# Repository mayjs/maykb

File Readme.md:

#  Maykb - a custom split keyboard for ISO-DE users
Maykb is a split keyboard using a staggered ISO layout including the ISO-Enter. Other features are one duplicated column in the middle (for people who don't always use the same finger for those middle keys) and the inclusion of an additional key left of the `h` which I use as a backspace key.

## PCB
The PCBs for maykb are based on a STM32F103 and Cherry MX switches.
Both halves communicate using a UART interface and are equipped to be chainable, i.e. you could chain together more keyboards so you could add a numpad or a dedicated macropad if you wanted to.

There is also no fixed host MCU; both sides can act as the host and communicate over USB.

The initial revision of the PCB has one flaw: The voltage regulator for the MCU is not enabled properly due to a enable pin polarity mistake. Fixing this mistake involves lifting a pin of that regulator and wiring it properly.
I plan to replace the regulator eventually and fix the schematic and layout at that point as well.
As far as I know, there are no other hardware issues that would keep you from building one of these keyboards.

## Firmware
### Application
The firmware for the keyboard is written in Rust and uses [keyberon](https://github.com/TeXitoi/keyberon).
You need to build two different firmware versions for the left and right side so the firmware knows which part of the matrix it's working on.

### Bootloader
I'm using a slightly modified version of the [stm32duino-bootloader](https://github.com/rogerclarkmelbourne/STM32duino-bootloader).
This allows easy DFU flashing when you change the firmware.
The bootloader can be entered by holding the top left key of each side or by holding down the bootloader key on the bottom side of the PCB.

## Construction
The maykb case is designed to be 3D-printed and design files are available as OpenSCAD code.
It should be easy to adjust the code to allow for different screw tolerances or even brass screw inserts.

As a small novelty, the plates can be manufactured as aluminium PCBs (I had good results with JLCPCB), which is cheaper than all laser cutting services I was able to locate.
It should also be possible to export the plate PCB files as a DXF file and use another fabrication technique.

The PCB is a simple 1.6mm thick two layer PCB and should be easily manufactured at any prototyping company.

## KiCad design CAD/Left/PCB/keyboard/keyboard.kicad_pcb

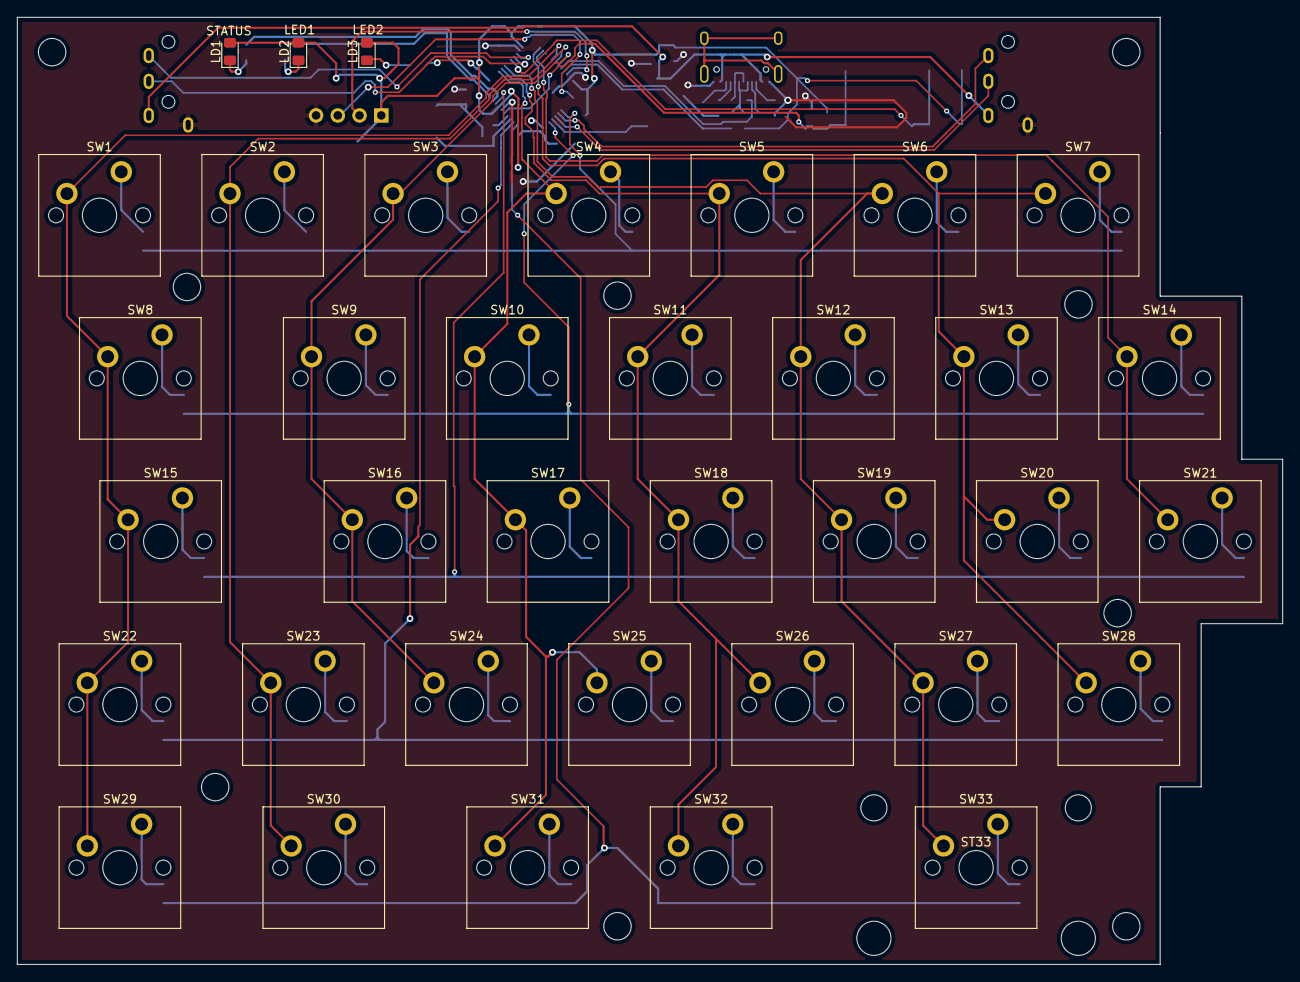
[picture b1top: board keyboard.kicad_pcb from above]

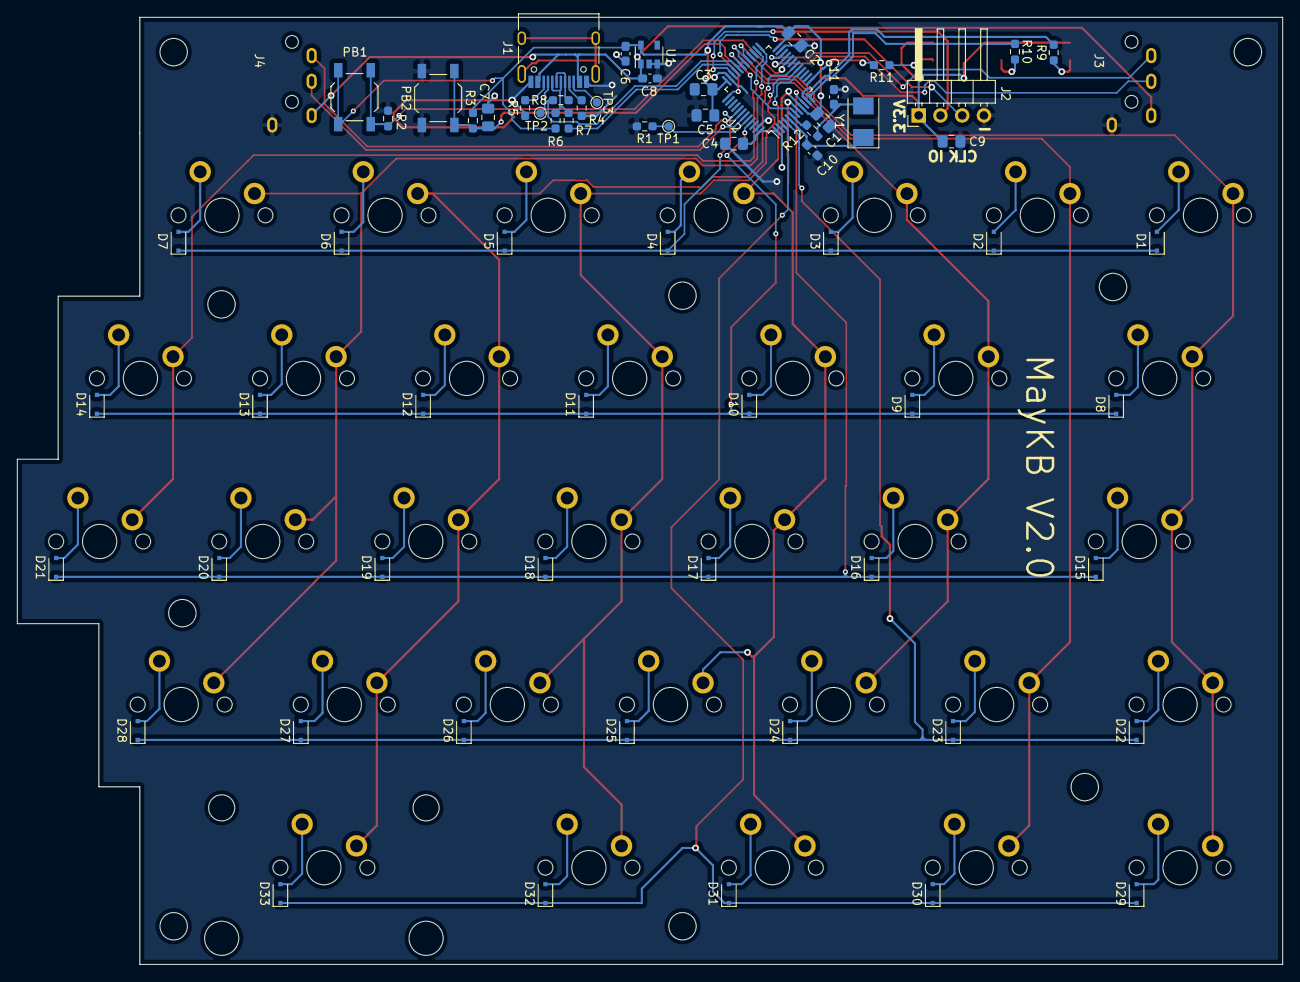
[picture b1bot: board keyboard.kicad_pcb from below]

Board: 2 copper layers, 147.8 x 110.6 mm, 105 parts (68 on the bottom side), 75 nets.

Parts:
C1, C2, C3, C4, C7, C9: 100nF; C_0805_2012Metric_Pad1.18x1.45mm_HandSolder
C5: 4.7uF - 10uF; C_0805_2012Metric_Pad1.18x1.45mm_HandSolder
C6, C8: 1uF; C_0603_1608Metric_Pad1.08x0.95mm_HandSolder
C10: CL1; C_0603_1608Metric_Pad1.08x0.95mm_HandSolder
C11: CL2; C_0603_1608Metric_Pad1.08x0.95mm_HandSolder
D1, D2, D3, D4, D5, D6, D7, D8, D9, D10, D11, D12, D13, D14, D15, D16, D17, D18, D19, D20, D21, D22, D23, D24, D25, D26, D27, D28, D29, D30, D31, D32, D33: D; D_SOD-323F
J1: USB_C_Receptacle_USB2.0; USB_C_Receptacle_HRO_TYPE-C-31-M-12
J2: Debug; PinHeader_1x04_P2.54mm_Horizontal
J3: Conn_Left; PJ-3200B-4A-TRRS
J4: Conn_Right; PJ-3200B-4A-TRRS
LD1, LD2, LD3: LED; LED_0805_2012Metric_Pad1.15x1.40mm_HandSolder
PB1: SW_SPST; SW_SPST_TL3342
PB2: RESET; SW_SPST_TL3342
R1, R2, R3: 10k; R_0603_1608Metric_Pad0.98x0.95mm_HandSolder
R4, R5: 5.1k; R_0603_1608Metric_Pad0.98x0.95mm_HandSolder
R6: 1.5k; R_0603_1608Metric_Pad0.98x0.95mm_HandSolder
R7, R8: 20R; R_0603_1608Metric_Pad0.98x0.95mm_HandSolder
R9, R10, R11: 510R; R_0603_1608Metric_Pad0.98x0.95mm_HandSolder
R12: RExt; R_0603_1608Metric_Pad0.98x0.95mm_HandSolder
ST33: MountingHole; Stabilizer_Cherry_MX_2u
SW1, SW2, SW3, SW4, SW5, SW6, SW7, SW9, SW10, SW11, SW12, SW13, SW14, SW16, SW17, SW18, SW19, SW20, SW21, SW23, SW24, SW25, SW26, SW27, SW28, SW32: SW_Push; SW_Cherry_MX_PCB_1.00u
SW8: SW_Push; SW_Cherry_MX_PCB_1.50u
SW15: SW_Push; SW_Cherry_MX_PCB_1.75u
SW22, SW29, SW30, SW31: SW_Push; SW_Cherry_MX_PCB_1.25u
SW33: SW_Push; SW_Cherry_MX_PCB_2.25u
TP1: TestPoint; TestPoint_Pad_D1.0mm
TP2: USB_SBU1; TestPoint_Pad_D1.0mm
TP3: USB_SBU2; TestPoint_Pad_D1.0mm
U1: LN1154; SOT-23-5
U2: STM32F103C8Tx; LQFP-48_7x7mm_P0.5mm
Y1: 8MHz; Crystal_SMD_5032-2Pin_5.0x3.2mm

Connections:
+3V3: C1.1, C2.1, C3.2, C4.1, C5.1, C6.1, C9.1, J2.1, LD1.2, LD2.2, LD3.2, PB1.2, R3.1, R6.1, U1.5, U2.1, U2.9, U2.24, U2.36, U2.48
+5V: C8.1, J1.A4, J1.A9, J1.B4, J1.B9, J3.T, J4.T, U1.1
/BOOT0: R1.1, TP1.1, U2.44
/BOOT1: PB1.1, R2.1, U2.20
/LED1: R10.2, U2.12
/LED2: R11.2, U2.13
/LED_STATUS: R9.2, U2.11
/LEFT_RX: J3.R2, U2.22
/LEFT_TX: J3.R1, U2.21
/NRST: C7.1, PB2.2, R3.2, U2.7
/OSCIN: C10.1, U2.5, Y1.1
/OSCOUT: R12.1, U2.6
/RIGHT_RX: J4.R1, U2.43
/RIGHT_TX: J4.R2, U2.42
/SWDCLK: J2.3, U2.37
/SWDIO: J2.2, U2.34
/UDM: R8.1, U2.32
/UDP: R7.1, U2.33
/USBDM: J1.A7, J1.B7, R8.2
/USBDP: J1.A6, J1.B6, R6.2, R7.2
COL0: SW1.1, SW8.1, SW15.1, SW22.1, SW29.1, U2.29
COL1: SW2.1, SW23.1, SW30.1, U2.30
COL2: SW3.1, SW9.1, SW16.1, SW24.1, U2.31
COL3: SW4.1, SW10.1, SW17.1, SW25.1, SW31.1, U2.16
COL4: SW5.1, SW11.1, SW18.1, SW26.1, SW32.1, U2.17
COL5: SW6.1, SW12.1, SW19.1, SW27.1, SW33.1, U2.18
COL6: SW7.1, SW13.1, SW20.1, SW28.1, U2.25
COL7: SW14.1, SW21.1, U2.26
GND: C1.2, C2.2, C3.1, C4.2, C5.2, C6.2, C7.2, C8.2, C9.2, C10.2, C11.1, J1.A1, J1.A12, J1.B1, J1.B12, J2.4, J3.S, J4.S, PB2.1, R1.2, R2.2, R4.1, R5.1, U1.2, U1.3, U2.8, U2.23, U2.35, U2.47
unnamed: D1.2, SW1.2
unnamed: D2.2, SW2.2
unnamed: D3.2, SW3.2
unnamed: D4.2, SW4.2
unnamed: D5.2, SW5.2
unnamed: D6.2, SW6.2
unnamed: D7.2, SW7.2
unnamed: D8.2, SW8.2
unnamed: D9.2, SW9.2
unnamed: D10.2, SW10.2
unnamed: D11.2, SW11.2
unnamed: D12.2, SW12.2
unnamed: D13.2, SW13.2
unnamed: D14.2, SW14.2
unnamed: D15.2, SW15.2
unnamed: D16.2, SW16.2
unnamed: D17.2, SW17.2
unnamed: D18.2, SW18.2
unnamed: D19.2, SW19.2
unnamed: D20.2, SW20.2
unnamed: D21.2, SW21.2
unnamed: D22.2, SW22.2
unnamed: D23.2, SW23.2
unnamed: D24.2, SW24.2
unnamed: D25.2, SW25.2
unnamed: D26.2, SW26.2
unnamed: D27.2, SW27.2
unnamed: D28.2, SW28.2
unnamed: D29.2, SW29.2
unnamed: D30.2, SW30.2
unnamed: D31.2, SW31.2
unnamed: D32.2, SW32.2
unnamed: D33.2, SW33.2
unnamed: C11.2, R12.2, Y1.2
unnamed: J1.A5, R4.2
unnamed: J1.A8, TP2.1
unnamed: J1.B5, R5.2
unnamed: J1.B8, TP3.1
unnamed: LD1.1, R9.1
unnamed: LD2.1, R10.1
unnamed: LD3.1, R11.1
ROW0: D1.1, D2.1, D3.1, D4.1, D5.1, D6.1, D7.1, U2.41
ROW1: D8.1, D9.1, D10.1, D11.1, D12.1, D13.1, D14.1, U2.45
ROW2: D15.1, D16.1, D17.1, D18.1, D19.1, D20.1, D21.1, U2.10
ROW3: D22.1, D23.1, D24.1, D25.1, D26.1, D27.1, D28.1, U2.4
ROW4: D29.1, D30.1, D31.1, D32.1, D33.1, U2.3

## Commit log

2021-09-11 Added v2.0 PCB designs. Note: The voltage regulator is not working in this design
2021-09-11 Added Plate designs. Plates are meant to be manufactured as aluminum PCBs
2021-09-11 Added schematic of the shared control circuitry
2021-09-11 Added a simple script to extract footprint positions from keycad footprint reports
2021-09-11 Added KLE layout JSON files
2021-09-11 Added case design files
2021-09-11 Added CAD license information
2021-09-11 Added bootloader
2021-09-11 Added keyberon based firmware
2021-09-11 Added license for the software parts
2021-10-28 Added a Readme
2021-10-28 Added sentence about special features
